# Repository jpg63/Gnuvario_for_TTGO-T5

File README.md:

# Gnuvario_for_TTGO-T5	DEVELOPPEMENT
# GNUVARIO-E     Stable version 0.3
# GNUVARIO-E     Developement version 0.7 beta 8
# PCB            version 2.00
# 3D CASE        version 2.00

Le Gnuvario-E est un projet openSource de variometre

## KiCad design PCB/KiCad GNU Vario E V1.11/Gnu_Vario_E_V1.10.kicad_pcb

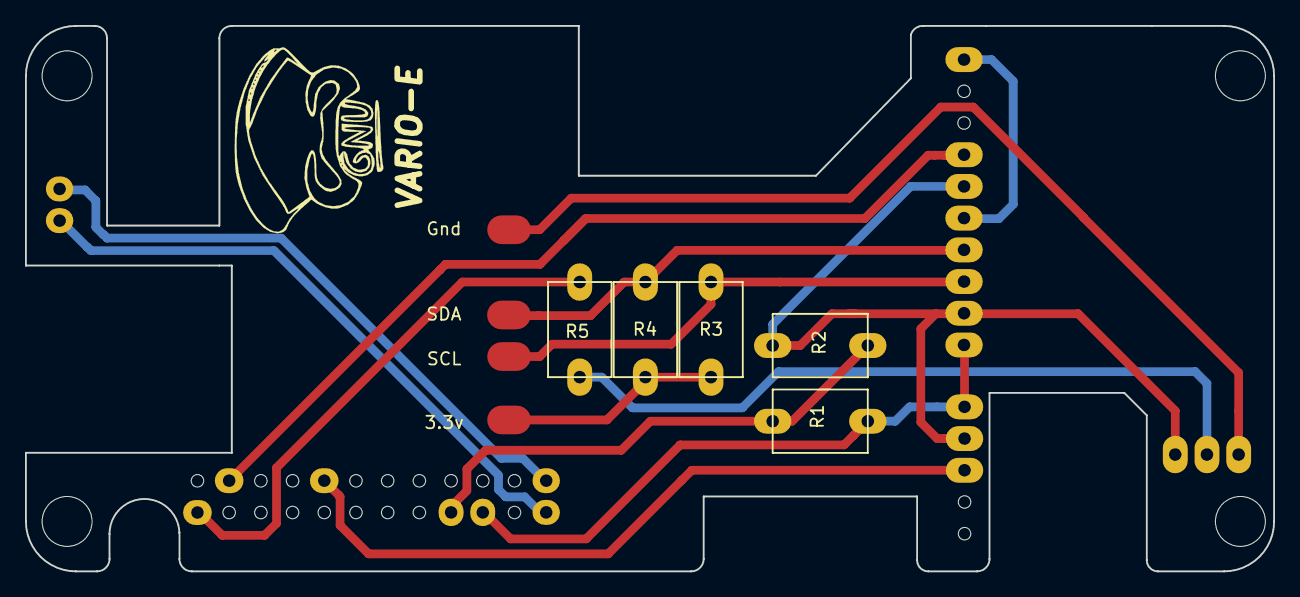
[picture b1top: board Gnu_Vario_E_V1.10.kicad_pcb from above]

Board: 2 copper layers, 100.0 x 43.7 mm, 11 parts (0 on the bottom side), 14 nets.

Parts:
BCxxx1: S8050; Transistor
CJMCU_117: MPU-9250+MS5611; CJMCU-117
GPS1: ATGM336H; GPS
J1: Pads connection; Pads_connection
R1: 270k; R1
R2: 1M; R1
R3, R4: 4.7k; R1
R5: 1K; R1
Speaker1: 4-8 ohms; Speaker
TTGO_T5_V1.x1: NIL; TTGO_T5_V1.x

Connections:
unnamed: BCxxx1.1, J1.1
unnamed: BCxxx1.2, R5.2
unnamed: BCxxx1.3, CJMCU_117.2, CJMCU_117.6, GPS1.2, R2.1
unnamed: CJMCU_117.1, GPS1.1, R1.2, TTGO_T5_V1.x1.3
unnamed: CJMCU_117.3, J1.4, R3.1
unnamed: CJMCU_117.4, J1.3, R4.1
unnamed: CJMCU_117.7, TTGO_T5_V1.x1.23
unnamed: CJMCU_117.5, CJMCU_117.10
unnamed: GPS1.3, TTGO_T5_V1.x1.20
unnamed: J1.5, R3.2, R4.2
unnamed: R1.1, R2.2, TTGO_T5_V1.x1.4
unnamed: R5.1, TTGO_T5_V1.x1.12
unnamed: Speaker1.1, TTGO_T5_V1.x1.13
unnamed: Speaker1.2, TTGO_T5_V1.x1.1

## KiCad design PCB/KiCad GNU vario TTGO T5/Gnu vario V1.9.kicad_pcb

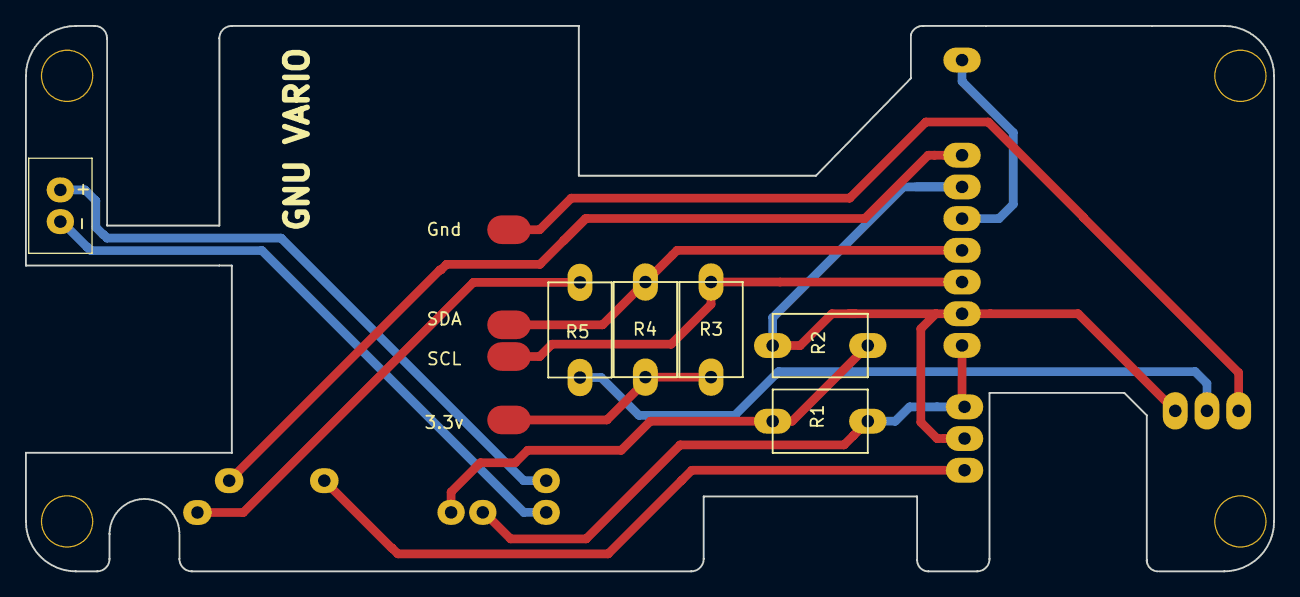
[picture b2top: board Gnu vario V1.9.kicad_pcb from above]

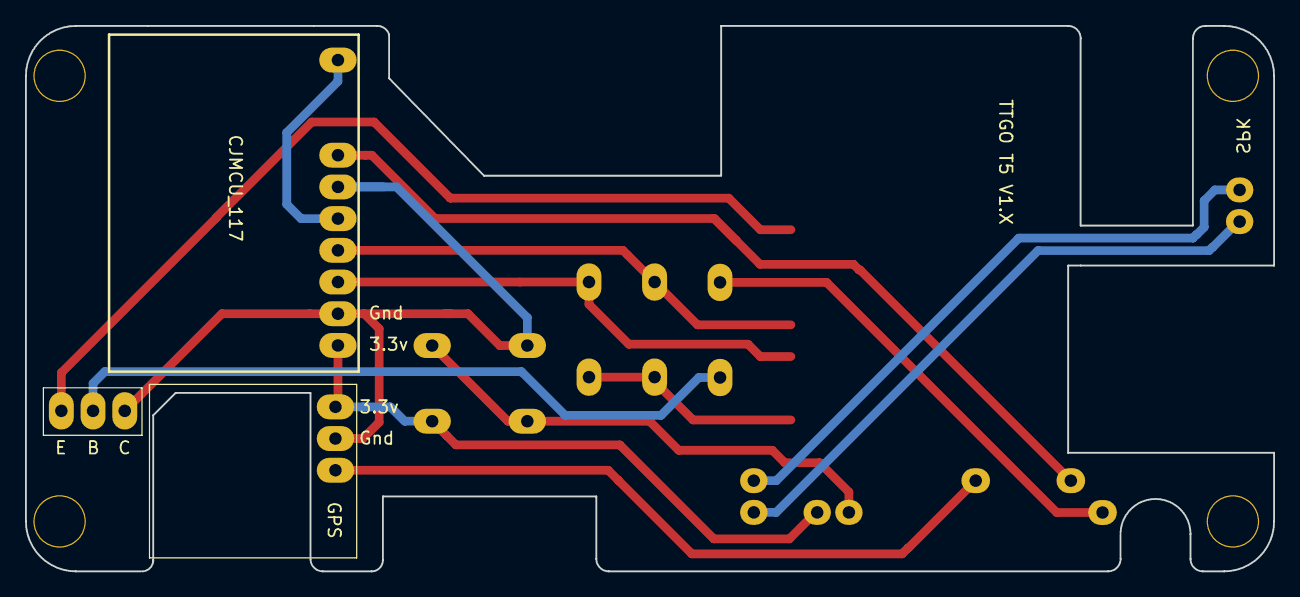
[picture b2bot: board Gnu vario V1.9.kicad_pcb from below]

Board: 2 copper layers, 100.0 x 43.7 mm, 11 parts (2 on the bottom side), 14 nets.

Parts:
J1: Conn_01x05; PinHeader_1x05_P2.54mm_Vertical_ttgo
Q1: S8050; Transistor
R1: 270k; R1
R2: 1M; R2
R3, R4: 4.7k; R1
R5: 1K; R1
SPK: Speaker
TTGO T5 V1.X: TTGO_T5; TTGO_T5_V1.2v2
U1: CJMCU_117; CJMCU-1000F
U2: GPS

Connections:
unnamed: SPK.2, TTGO T5 V1.X.HP -
unnamed: R1.2, TTGO T5 V1.X.3, U1.1, U2.1
unnamed: R1.1, R2.2, TTGO T5 V1.X.4
unnamed: R5.1, TTGO T5 V1.X.12
unnamed: SPK.1, TTGO T5 V1.X.HP +
unnamed: TTGO T5 V1.X.20, U2.3
unnamed: TTGO T5 V1.X.23, U1.7
unnamed: J1.1, Q1.1
unnamed: J1.3, R4.1, U1.4
unnamed: J1.4, R3.1, U1.3
unnamed: J1.5, R3.2, R4.2
unnamed: Q1.2, R5.2
unnamed: Q1.3, R2.1, U1.2, U1.6, U2.2
unnamed: U1.5, U1.10

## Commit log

2019-04-02 First push
2019-04-02 Add Ide arduino information
2019-05-09 Add conception documents Maj lib and test code
2019-07-02 Ajout PCB, Schema, boitier 3D
2019-07-02 Maj PCB files
2019-07-02 Mise à jour PCB, schema, boitier 3D, librairies Ajout Code Gnuvario-E
2019-07-03 Maj Boitier 3D v1.03
2019-07-03 Code Version 0.4 beta 1
2019-07-03 Ajout photo boitier
2019-07-05 PCB V1.10
2019-07-05 3D CASE V1.04
2019-07-05 Stable Version 0.3
2019-07-05 Beta Version 0.4 beta 1
2019-07-05 Reorganization code source add test code
2019-07-05 folder Reorganization
2019-07-10 Beta Version 0.4 beta 2
2019-07-12 PCB - liste des composants 3D - version 1.05
2019-07-13 PCB Version 1.11
2019-07-22 Mise à jour README
2019-07-22 Beta Version 0.4 beta 4
2019-07-23 PCB - mise à jour liste des composants
2019-07-23 PCB - Ajout photos
2019-07-24 Beta Version 0.4 beta 5
2019-07-25 PCB - Version 1.12
2019-07-28 3D CASE V1.06
2019-07-28 PCB - ajout PCB pour Cnc
2019-07-28 3D CASE V 1.06 Maj
2019-08-06 Beta Version 0.4 beta 6
2019-08-06 SOURCE - Beta Version 0.4 beta 7
2019-08-06 SOURCE - Code de test - Test serveur Web
2019-08-06 Maj Readme
2019-08-08 SOURCE - Beta version 0.4 beta 8
2019-08-18 Ajout doc TTGO-T5 / photos
2019-08-24 SOURCE - Beta Version 0.5 beta 2
2019-08-27 SOURCE - Beta Version 0.5 beta 3
2019-08-30 SOURCE - Beta Version 0.5 beta 4
2019-08-31 SOURCE - Beta Version 0.5 beta 5
2019-09-02 PCB - cleanup
2019-09-05 SOURCE - Beta Version 0.5 beta 6
2019-09-20 SOURCE - Beta Version 0.5 Beta 7
2019-09-22 SOURCE - Beta Version 0.5 Beta 8
2019-09-25 SOURCE - Beta Version 0.5 Beta 9
2019-09-26 Ajout fiche de présentation
2019-10-02 SOURCE - Beta Version 0.6 Beta 1
2019-10-12 SOURCE - Ajout dossier pour la SDCARD
2019-10-12 SOURCE - Beta Version 0.6 beta 2
2019-10-12 modification SDROOT
2019-10-23 BOITIER - Version 2.00
2019-10-23 PCB - Version 2.00
2019-10-23 SOURCE - Beta Version 0.6 beta 3
2019-11-01 SOURCE - Beta Version 0.6 beta 4
2019-11-04 Ajout ecran, rootsd
2019-11-05 BOITIER - MAJ
2019-11-12 BOITIER - Version 2.01
2019-11-16 SOURCE - Beta Version 0.6 beta 6
2019-11-28 SOURCE - Beta Version 0.6 beta 7
2019-11-30 BOITIER - MAJ ecran 2.9
2019-12-01 GNU slide switch cap shorter
2019-12-03 BOITIER - MAJ bouton
2019-12-24 SOURCE - Beta Version 0.7 beta 3
2019-12-29 2.9" and 1.54" screen bugs removed
2020-01-04 SOURCE - Beta Version 0.7 beta 4
2020-01-09 SOURCE - Beta Version 0.7 beta 5
2020-01-11 SOURCE - Beta Version 0.7 beta 6
2020-01-17 SOURCE - Add firmware.json
2020-02-05 SOURCE - Beta Version 0.7 beta 8
2020-02-22 SOURCE - Beta Version 0.7 beta 8 - correction parser
2020-02-25 SOURCE - Beta Version 0.7 beta 8 - correction parser / Correction screen 291
2020-02-25 SOURCE - Beta Version 0.7 beta 8 - Modif varioscreen
2020-03-01 SOURCE - Beta Version 0.7 beta 8 - Maj calibration / mise à jour auto
2020-03-02 SOURCE - Beta Version 0.7 beta 8 - Ajout calibration
2020-03-03 SOURCE - Beta Version 0.7 beta 8 - correction bug
2020-03-07 SOURCE - Beta Version 0.7 beta 8 - ajout xsemaphore
2020-03-08 SOURCE - Beta Version 0.7 beta 8 - Maj GxEpd2 + correction Bug
2020-03-10 SOURCE - Beta Version 0.7 beta 8 - ajout calibration baro manuelle
2020-03-15 PCB - Mise à jour v2.0
2020-03-24 SOURCE - Beta Version 0.8 beta 1
2020-04-06 SOURCE - Beta 0.8 beta 1 - correction blocage MS5611
2020-04-08 SOURCE - Beta 0.8 beta 1 - correction affichage des titres
2020-04-12 SOURCE - Beta 0.8 beta 1 - multi-langue
2020-04-13 SOURCE - Beta 0.8 beta 1
2020-04-21 SOURCE - Beta 0.8 beta 1 Vscode
2020-04-27 SOURCE - Beta 0.8 beta 1 - Maj ecran 1.54''
2020-04-28 SOURCE - Beta 0.8 beta 1 - Maj
2020-05-15 SOURCE - Beta 0.8 beta 1 et beta 2
2020-05-16 SOURCE - Beta 0.8 beta 2
2020-05-26 SOURCE - Beta 0.8 beta 3
2020-08-04 SOURCE - Beta 0.8 beta 3 Code en test
2020-08-05 SOURCE - Beta rootSD
2020-09-15 SOURCE - Beta Version 0.8 beta 4
2020-11-15 SOURCE - Beta Version 0.8 beta 5
2021-04-12 SOURCE BETA - version 0.8 beta 6
2021-06-27 SOURCE BETA - version 0.8 beta 6 - correction cap + bugs
2021-06-29 ROOTSD - 0.8 beta 6
2021-06-29 WWW.GZ - version 0.8b6
